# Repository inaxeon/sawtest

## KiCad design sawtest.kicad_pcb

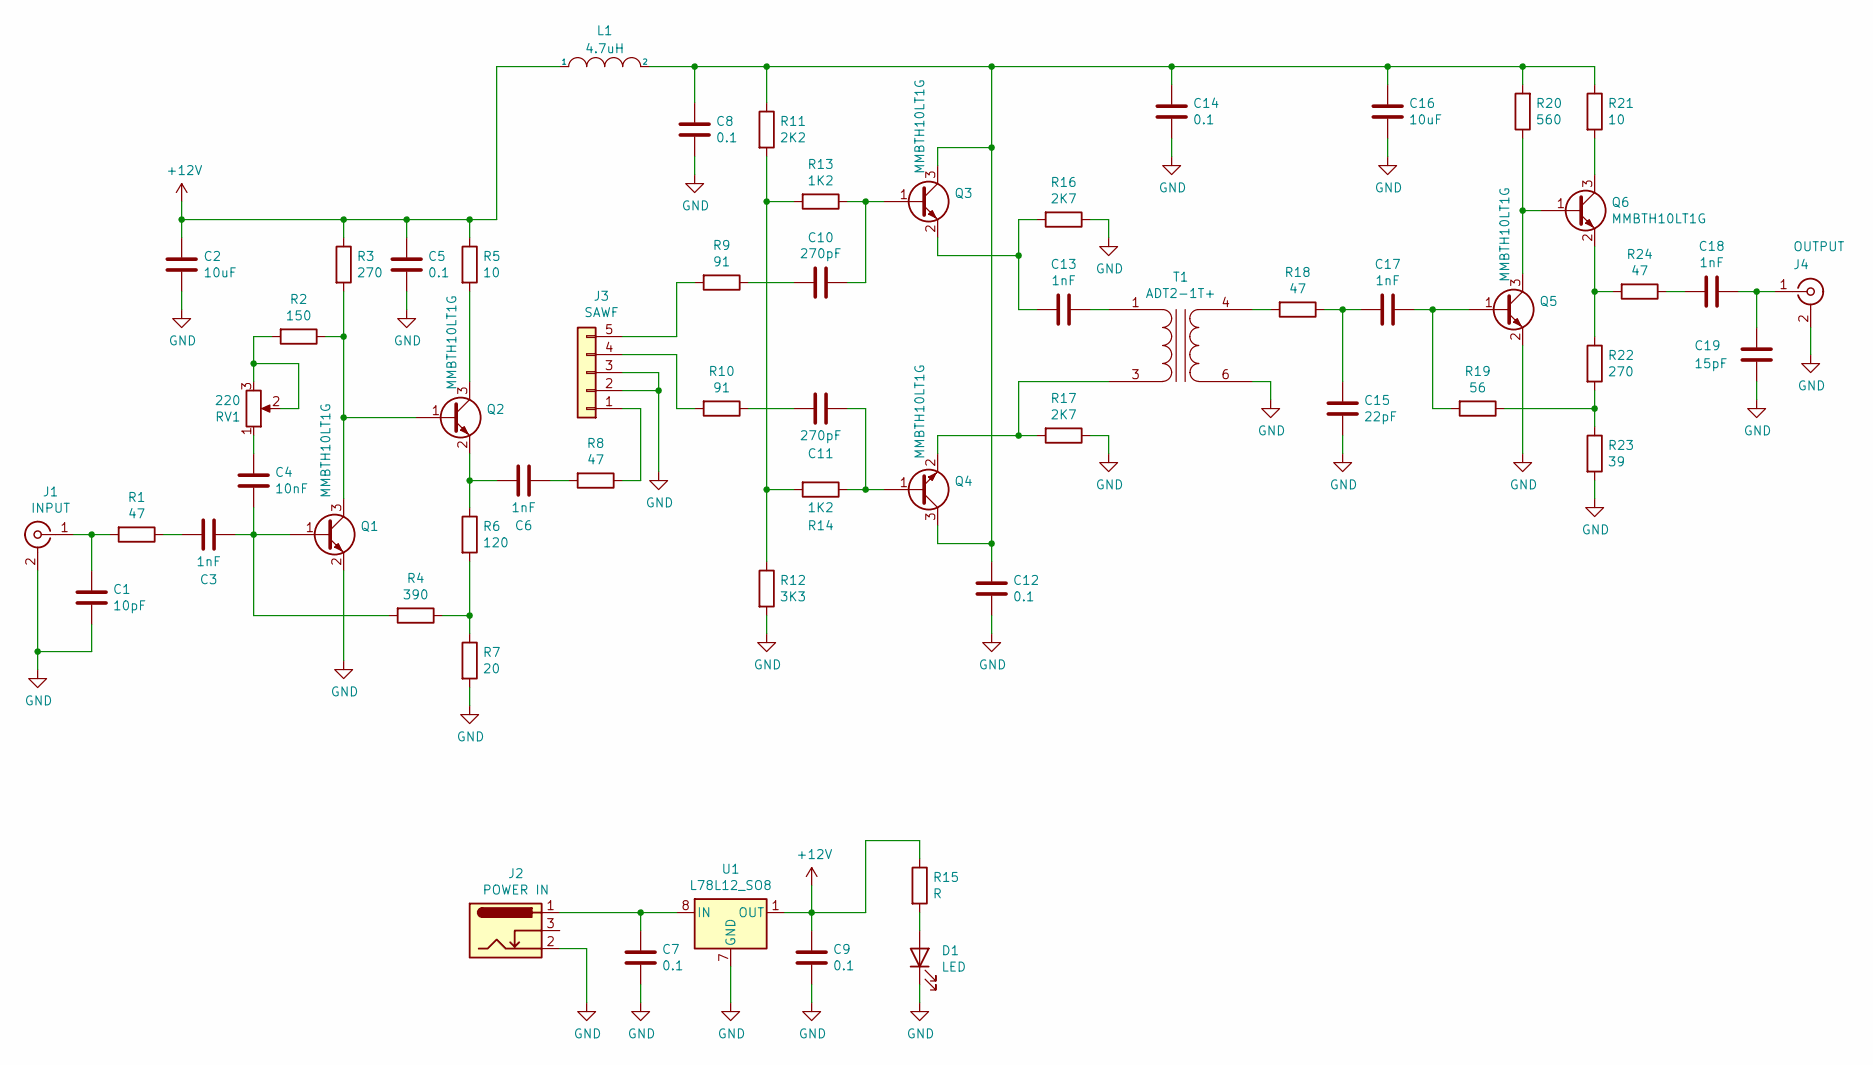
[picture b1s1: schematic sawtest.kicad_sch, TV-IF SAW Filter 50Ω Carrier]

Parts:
C1: 10pF; C_0603_1608Metric
C2, C16: 10uF; C_1210_3225Metric
C3, C6, C13, C17, C18: 1nF; C_0603_1608Metric
C4: 10nF; C_0603_1608Metric
C5, C7, C8, C9, C12, C14: 0.1; C_0603_1608Metric
C10, C11: 270pF; C_0603_1608Metric
C15: 22pF; C_0603_1608Metric
C19: 15pF; C_0603_1608Metric
D1: LED; LED_0805_2012Metric
J1: INPUT; SMA_Molex_73251-2200_Horizontal
J2: POWER IN; DC_JACK
J3: SAWF; PinSocket_1x05_P2.54mm_Vertical
J4: OUTPUT; SMA_Molex_73251-2200_Horizontal
L1: 4.7uH; L_0805_2012Metric
Q1, Q2, Q3, Q4, Q5, Q6: MMBTH10LT1G; SOT-23
R1, R8, R18, R24: 47; R_0603_1608Metric
R2: 150; R_0603_1608Metric
R3, R22: 270; R_0603_1608Metric
R4: 390; R_0603_1608Metric
R5, R21: 10; R_0603_1608Metric
R6: 120; R_0603_1608Metric
R7: 20; R_0603_1608Metric
R9, R10: 91; R_0603_1608Metric
R11: 2K2; R_0603_1608Metric
R12: 3K3; R_0603_1608Metric
R13, R14: 1K2; R_0603_1608Metric
R15: R; R_0603_1608Metric
R16, R17: 2K7; R_0603_1608Metric
R19: 56; R_0603_1608Metric
R20: 560; R_0603_1608Metric
R23: 39; R_0603_1608Metric
RV1: 220; Potentiometer_Bourns_3314G_Vertical
T1: ADT2-1T+; ADT4
U1: L78L12_SO8; SOIC-8_3.9x4.9mm_P1.27mm

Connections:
+12V: C2.1, C5.1, C9.1, L1.1, R3.1, R5.1, R15.1, U1.1 (OUT)
GND: C1.2, C2.2, C5.2, C7.2, C8.2, C9.2, C12.2, C14.2, C15.2, C16.2, C19.2, D1.1 (K), J1.2 (Ext), J2.2, J3.2, J3.3, J4.2 (Ext), Q1.2 (E), Q5.2 (E), R7.2, R12.2, R16.1, R17.1, R23.2, T1.6 (SA), U1.2 (GND), U1.3 (GND), U1.6 (GND), U1.7 (GND)
unnamed: C3.1, R1.1
unnamed: C4.1, RV1.1
unnamed: C6.1, R8.2
unnamed: C10.2, R9.1
unnamed: C11.2, R10.1
unnamed: C15.1, C17.2, R18.1
unnamed: C18.2, R24.1
unnamed: D1.2 (A), R15.2
unnamed: C1.1, J1.1 (In), R1.2
unnamed: J3.1, R8.1
unnamed: J3.4, R10.2
unnamed: J3.5, R9.2
unnamed: C18.1, C19.1, J4.1 (In)
unnamed: C3.2, C4.2, Q1.1 (B), R4.2
unnamed: Q1.3 (C), Q2.1 (B), R2.1, R3.2
unnamed: Q2.3 (C), R5.2
unnamed: C6.2, Q2.2 (E), R6.1
unnamed: C10.1, Q3.1 (B), R13.1
unnamed: C8.1, C12.1, C14.1, C16.1, L1.2, Q3.3 (C), Q4.3 (C), R11.1, R20.2, R21.1
unnamed: C13.2, Q3.2 (E), R16.2
unnamed: C11.1, Q4.1 (B), R14.1
unnamed: Q4.2 (E), R17.2, T1.3 (AB)
unnamed: C17.1, Q5.1 (B), R19.2
unnamed: Q5.3 (C), Q6.1 (B), R20.1
unnamed: Q6.3 (C), R21.2
unnamed: Q6.2 (E), R22.1, R24.2
unnamed: R2.2, RV1.2, RV1.3
unnamed: R4.1, R6.2, R7.1
unnamed: R11.2, R12.1, R13.2, R14.2
unnamed: R19.1, R22.2, R23.1
unnamed: C13.1, T1.1 (AA)
unnamed: R18.2, T1.4 (SB)
unnamed: C7.1, J2.1, U1.8 (IN)

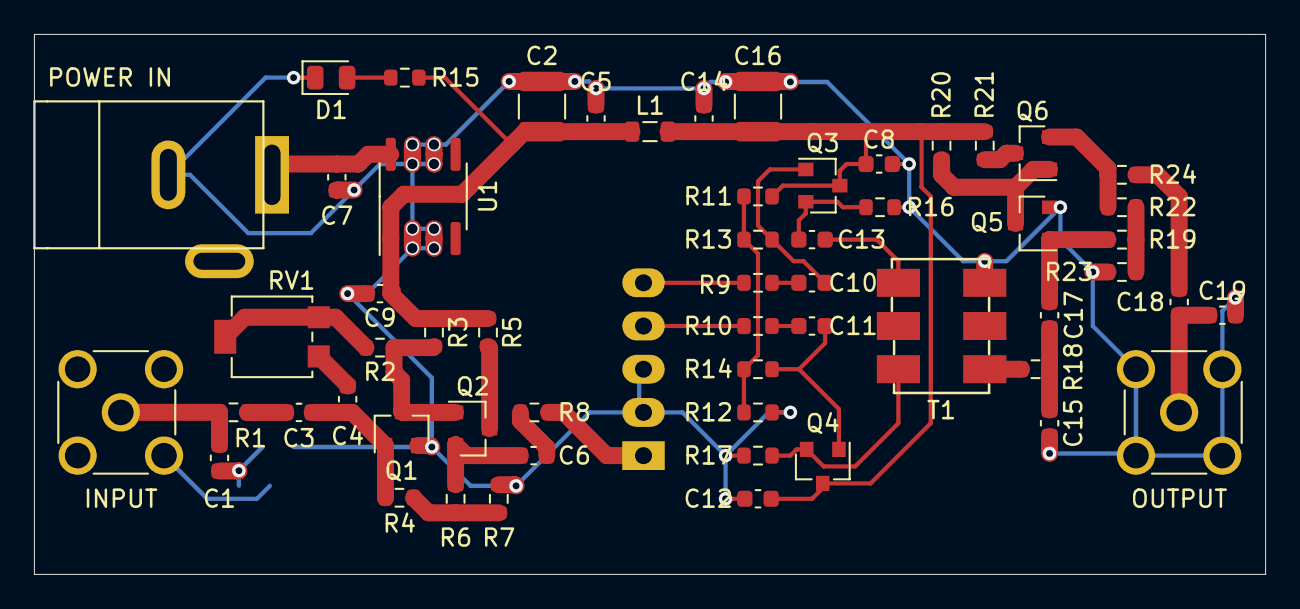
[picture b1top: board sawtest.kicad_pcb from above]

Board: 2 copper layers, 72.4 x 31.8 mm, 58 parts (0 on the bottom side), 35 nets.
